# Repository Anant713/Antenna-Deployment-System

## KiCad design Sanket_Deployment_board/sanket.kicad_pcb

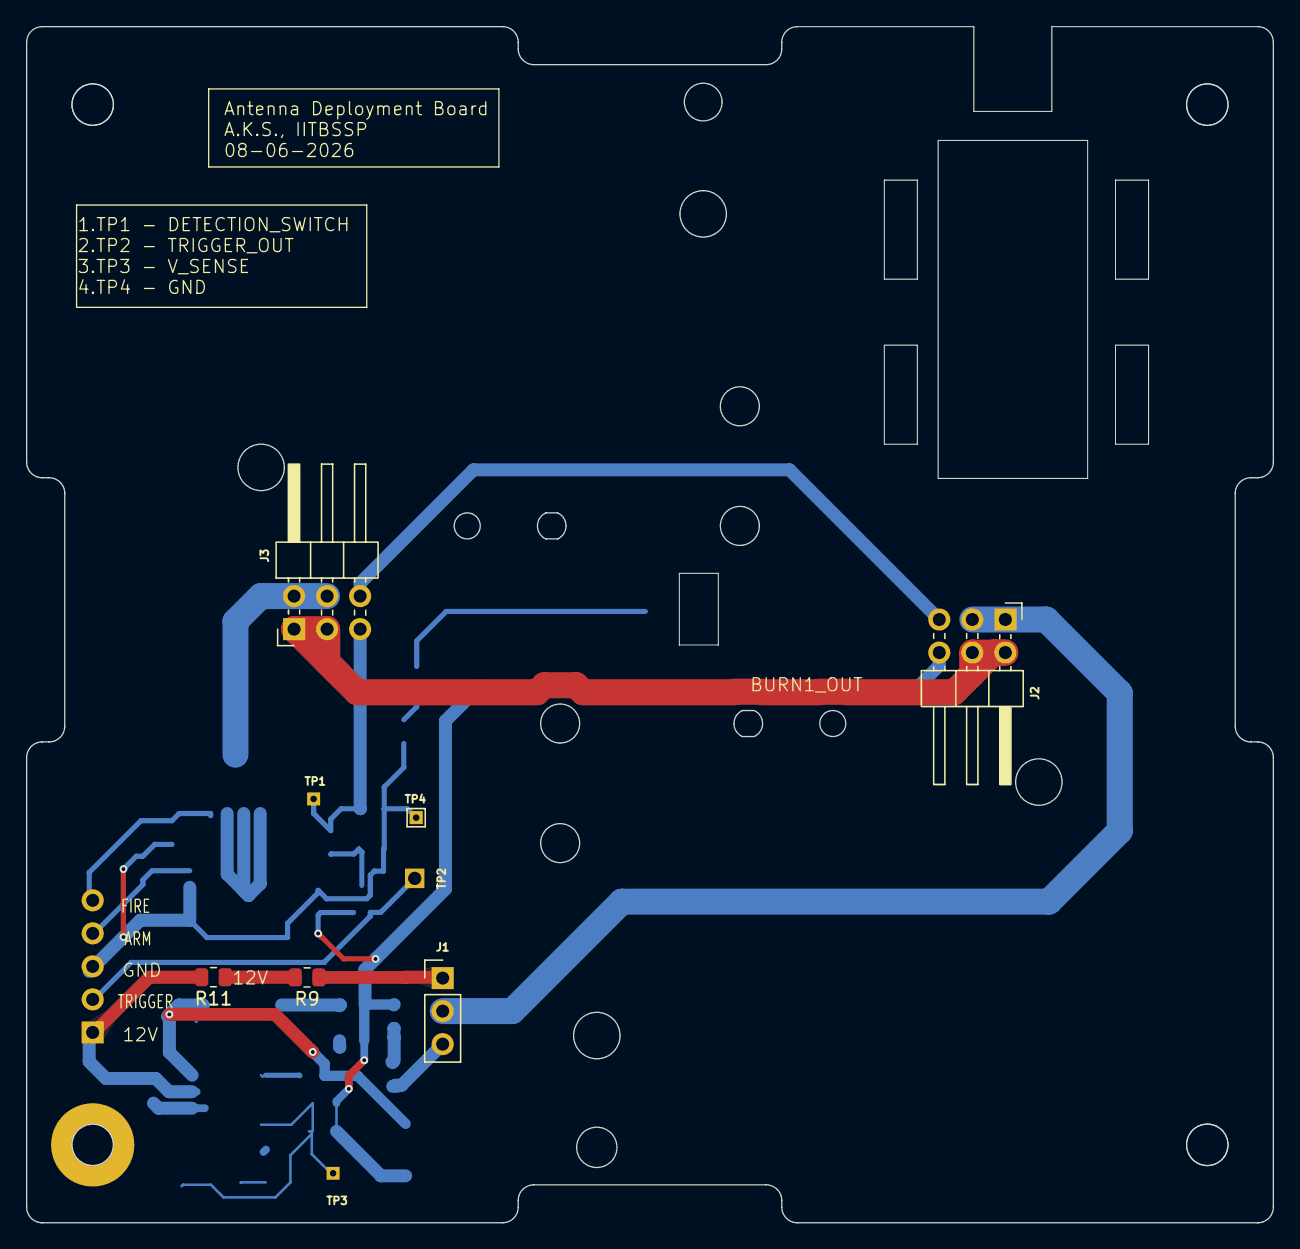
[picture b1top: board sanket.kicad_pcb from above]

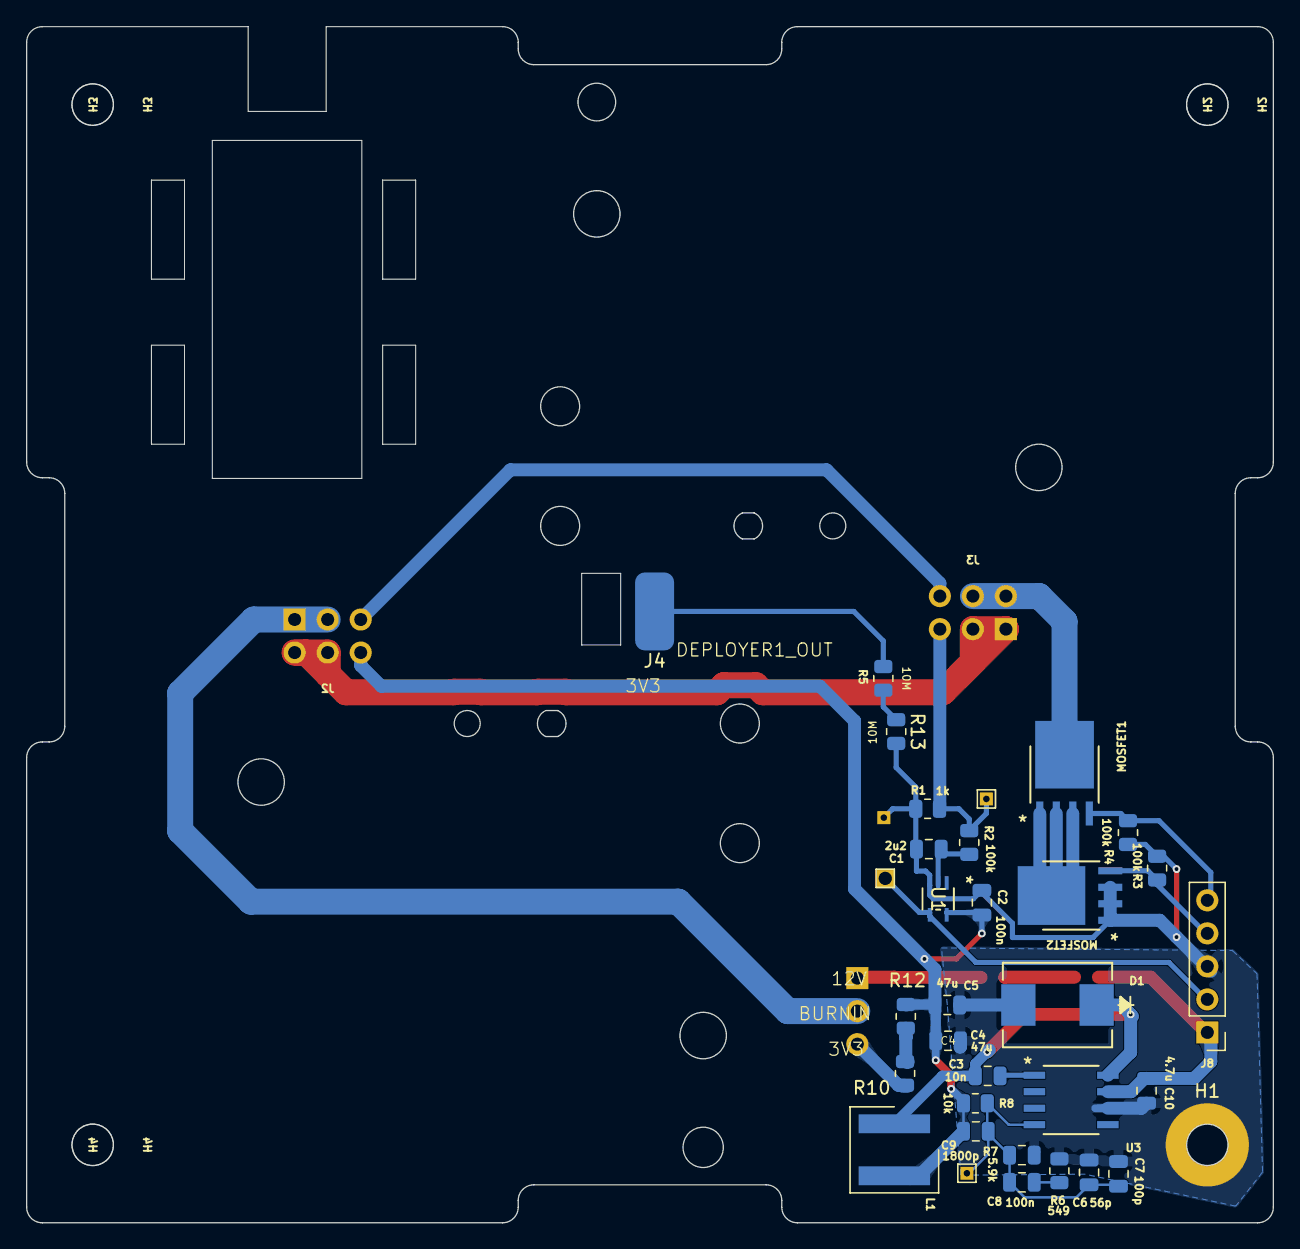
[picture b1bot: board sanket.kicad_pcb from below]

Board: 2 copper layers, 95.9 x 92.0 mm, 42 parts (32 on the bottom side), 23 nets.

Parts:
C1: 2u2; C_0805_2012Metric
C2, C8: 100n; C_0805_2012Metric
C3: 10n; C_0805_2012Metric
C4, C5: 47u; C_0805_2012Metric
C6: 56p; C_0805_2012Metric
C7: 100p; C_0805_2012Metric
C9: 1800p; C_0805_2012Metric
C10: 4.7u; C_0805_2012Metric
D1: CR_MBRS340_ONS-M
H1: MountingHole_Pad; MountingHole_3.2mm_M3_Pad
H2, H3, H4: MountingHole_3.2mm_M3
J1: PinHeader_1x03_P2.54mm_Vertical
J2, J3: Conn_02x03_Counter_Clockwise; PinHeader_2x03_P2.54mm_Horizontal
J4: SolderWirePad_1x01_SMD_3x6mm
J8: PinHeader_1x05_P2.54mm_Vertical
L1: 18uH; L_Wurth_WE-XHMI-6060P
MOSFET1, MOSFET2: BUK9Y21-40E_115; LFPAK56_SOT669_NEX-M
R1: 1k; R_0805_2012Metric
R2, R3, R4: 100k; R_0805_2012Metric
R5, R13: 10M; R_0805_2012Metric
R6: 549; R_0805_2012Metric
R7: 5.9k; C_0805_2012Metric
R8: 10k; R_0805_2012Metric
R9, R10, R11, R12: R; R_0805_2012Metric
TP1, TP2, TP3, TP4: TestPoint_THTPad_1.0x1.0mm_Drill0.5mm
U1: SN74LVC1G17QDCKRQ1; DCK5-M
U3: D8-M

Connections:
+3V3: C2.2, C4.2, C5.2, C9.1, J2.6, L1.2, R8.1, R12.1, U1.5 (VCC)
+12V: C10.1, J8.1, R11.2, U3.7 (VIN)
/ARM: J8.4, MOSFET2.4, R3.1
/BLEEDER: J4.1 (Pin_1_1), R5.1
/BurnWire1IN: J1.2, J2.1, J2.3
/BurnWire1OUT: J2.2, J2.4, J3.1, J3.3
/DeployerDetectionSW1OUT: J2.5, J3.6
/DeployerDetectionSW2OUT: J3.5, R1.1, R2.1, TP1.1 (1_1)
/FIRE: J8.5, MOSFET1.4, R4.1
/NMOS_DRAIN: J3.2, J3.4, MOSFET1.5
/TriggerOUT: J8.2, TP2.1 (1_1), U1.4 (Y)
GND: C1.1, C2.1, C4.1, C5.1, C6.1, C7.1, C10.2, D1.2 (A), H1.1 (1_1), J8.3, MOSFET2.1, MOSFET2.2, MOSFET2.3, R1.2, R3.2, R4.2, R6.2, R7.2, R13.2, TP4.1 (1_1), U1.3 (GND), U3.6 (GND)
unnamed: C8.1, R6.1
unnamed: C3.1, D1.1 (K), L1.1, U3.8 (PH)
unnamed: J1.1, R9.1
unnamed: J1.3, R10.1
unnamed: MOSFET1.1, MOSFET1.2, MOSFET1.3, MOSFET2.5
unnamed: R10.2, R12.2
unnamed: R9.2, R11.1
unnamed: R5.2, R13.1
unnamed: C1.2, R2.2, U1.2 (A)
unnamed: C3.2, U3.1 (BOOT)
unnamed: C6.2, C7.2, C8.2, C9.2, R7.1, R8.2, TP3.1 (1_1), U3.4 (VSNS)

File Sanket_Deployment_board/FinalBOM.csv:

"Reference","Value","Datasheet","Footprint","Qty","DNP"
"C1","2u2","","Capacitor_SMD:C_0805_2012Metric","1",""
"C2,C8","100n","","Capacitor_SMD:C_0805_2012Metric","2",""
"C3","10n","","Capacitor_SMD:C_0805_2012Metric","1",""
"C4,C5","47u","","Capacitor_SMD:C_0805_2012Metric","2",""
"C6","150p","","Capacitor_SMD:C_0805_2012Metric","1",""
"C9","1800p","","Capacitor_SMD:C_0805_2012Metric","1",""
"C10","4.7u","~","Capacitor_SMD:C_0805_2012Metric","1",""
"D1","D","~","Wurth inductor:DIOM7959X261N","1",""
"J1","Conn_01x03","~","Connector_PinHeader_2.54mm:PinHeader_1x03_P2.54mm_Vertical","1",""
"J2,J3","Conn_02x03_Counter_Clockwise","~","Connector_PinHeader_2.54mm:PinHeader_2x03_P2.54mm_Horizontal","2",""
"J4,J7","Conn_01x01_Socket","~","Connector_PinSocket_2.54mm:PinSocket_1x01_P2.54mm_Vertical","2",""
"J8","Conn_01x05","~","Connector_PinHeader_2.54mm:PinHeader_1x05_P2.54mm_Vertical","1",""
"L1","18u","~","Inductor_SMD_Wurth:L_Wurth_WE-XHMI-6060P","1",""
"Q1,Q2","NMOS","https://ngspice.sourceforge.io/docs/ngspice-html-manual/manu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","NMOS_sanket:LFPAK56_SOT669_NEX-M","2",""
"R1","1k","~","Resistor_SMD:R_0805_2012Metric","1",""
"R2,R3,R4","100k","~","Resistor_SMD:R_0805_2012Metric","3",""
"R5","1M","~","Resistor_SMD:R_0805_2012Metric","1",""
"R6","549","~","Resistor_SMD:R_0805_2012Metric","1",""
"R7","5.9K","~","Capacitor_SMD:C_0805_2012Metric","1",""
"R8","10k","~","Resistor_SMD:R_0805_2012Metric","1",""
"TP1,TP2,TP3,TP4","TestPoint","~","TestPoint:TestPoint_THTPad_1.0x1.0mm_Drill0.5mm","4",""
"U2","SN74LVC1G17QDCKRQ1","","Package_TO_SOT_SMD:SOT-353_SC-70-5","1",""
"U3","TPS5420D","http://www.ti.com/lit/ds/symlink/tps5420.pdf","Package_SO:SOIC-8_3.9x4.9mm_P1.27mm","1",""
"U4","74AHC1G00","http://www.ti.com/lit/sg/scyt129e/scyt129e.pdf","NAND_sanket:DCK5_TEX-L","1",""

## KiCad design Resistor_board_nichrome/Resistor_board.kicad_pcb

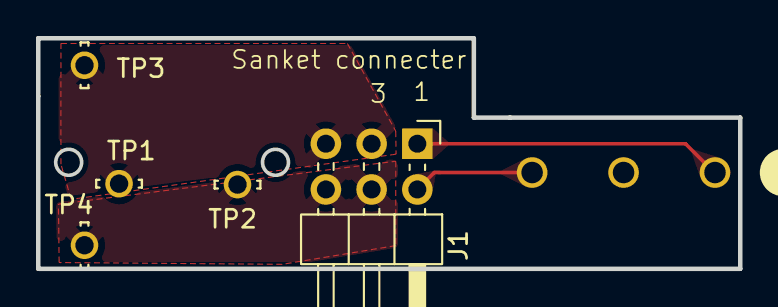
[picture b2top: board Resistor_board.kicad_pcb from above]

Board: 2 copper layers, 39.0 x 12.8 mm, 6 parts (1 on the bottom side), 4 nets.

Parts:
J1: Conn_01x06_Pin; PinHeader_2x03_P2.54mm_Horizontal
SW1: SW_SPDT_312; D2F-L_OMR
TP1, TP2, TP3, TP4: 5021; TP_5021

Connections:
/BurnWireIN: J1.3, J1.5, TP1.TP, TP3.TP
/DeployerDetectionSWIN: J1.2, SW1.3 (A)
/DeployerDetectionSWOUT: J1.1, SW1.1 (B)
/GND: J1.4, J1.6, TP2.TP, TP4.TP

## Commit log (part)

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2026-05-25 Resistor board completed. Main board schematic completed and footprints assigned
2026-05-25 Switch footprint flipped to opposite side, Edgecut layer updated according to new resistor board
2026-05-26 Routing done, 1st review to be done
2026-05-27 Added missing holw in resistor board, removed NAND gate, added more testpoints
2026-05-28 Added extra pads for sized resistors
2026-05-29 Resistor board for nichrome added
2026-06-05 Added antenna bleeder, switched FIRE and ARM with each other, Corrected Schmitt trigger symbol to non-inverting
2026-06-08 Replace a mounting hole to mounting pad to ground
2026-06-08 Added schematic pdf of Sanket
2026-06-09 Aligned holes according to PC104, flipped header used to choose burn power, corrected silkscreen
2026-06-16 Added step file for ADS_V8
2026-06-17 Cahnges dimensions of resistor boards due to clash with housing
2026-06-20 Added gerber and drill files , default settings completely
